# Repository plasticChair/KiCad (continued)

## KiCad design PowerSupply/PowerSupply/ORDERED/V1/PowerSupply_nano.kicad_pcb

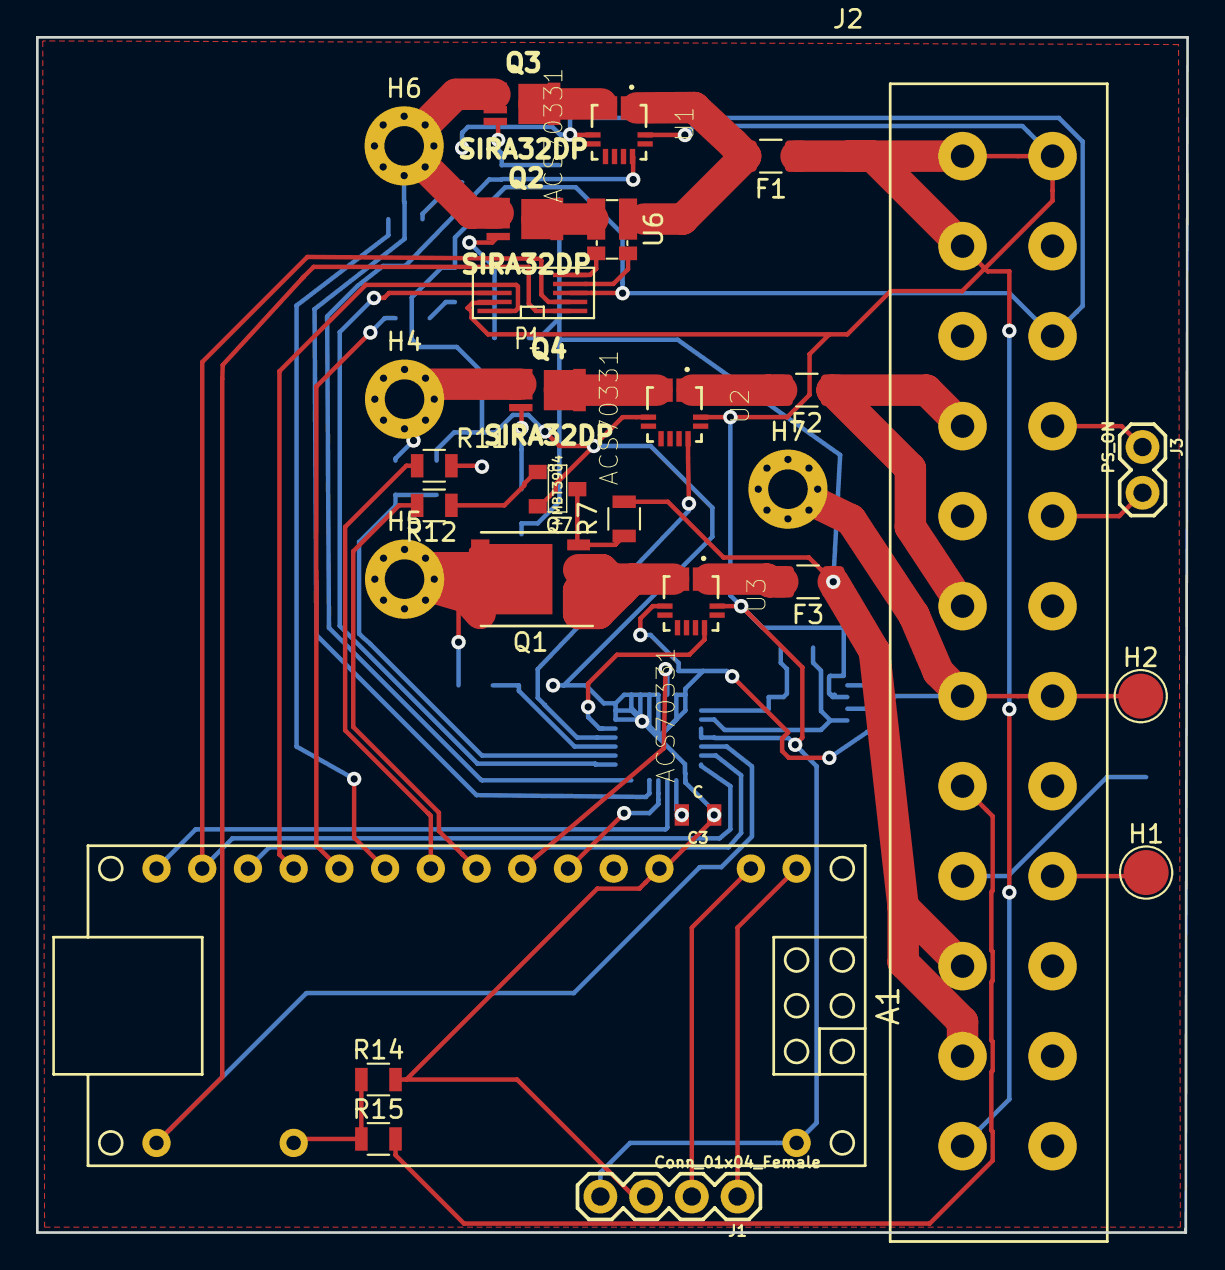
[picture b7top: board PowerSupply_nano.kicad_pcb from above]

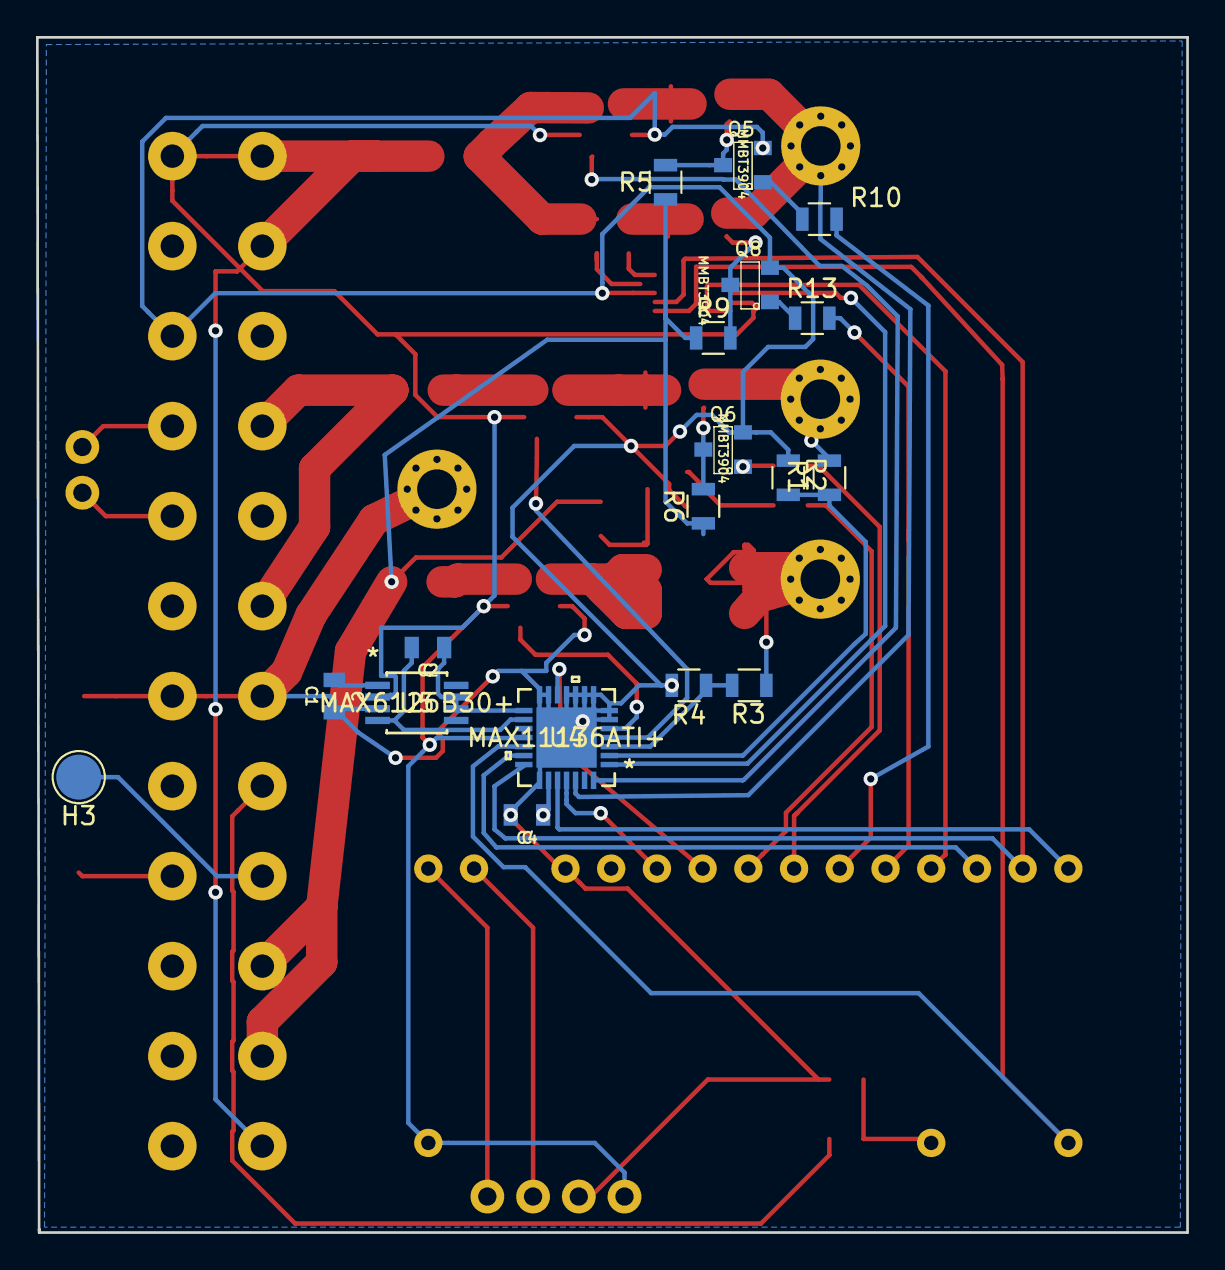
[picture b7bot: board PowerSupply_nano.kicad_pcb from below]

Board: 2 copper layers, 63.9 x 66.4 mm, 47 parts (18 on the bottom side), 53 nets.

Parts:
A1: Arduino_Nano_v3.x; arduino_nano
C1, C2, C3, C4: C; 0805
F1, F2, F3: Polyfuse; Fuse_1206_3216Metric
H1: 5V_load; TestPoint_Pad_D2.5mm
H2: 5V_load_GND; TestPoint_Pad_D2.5mm
H3: 5V_USB; TestPoint_Pad_D2.5mm
H4: 5V_OUT; MountingHole_2.2mm_M2_Pad_Via
H5: 12V_OUT; MountingHole_2.2mm_M2_Pad_Via
H6: 3p3V_OUT; MountingHole_2.2mm_M2_Pad_Via
H7: GND_OUT; MountingHole_2.2mm_M2_Pad_Via
J1: Conn_01x04_Female; 1X04
J2: ATX24; ATX_PWR_25pin
J3: PS_ON; 1X02
P1: MAX9939; uMAX-uSOP_10
Q1: SI7157DP; SO-8_PowerPAK_Vishay_Single
Q2, Q3, Q4: SIRA32DP; PowerPAK-1212-8
Q5, Q6, Q7, Q8: MMBT3904; SOT23
R1, R2, R3, R4, R5, R6, R7, R9: 10k; R_0805
R10, R11, R12, R13: 2.2k; R_0805
R14, R15: R; R_0805
U1, U2, U3: ACS70331; ALLEGRO_ACS70331EESATR-005U3
U4: MAX11136ATI+; MAX11136ATI&plus_
U5: MAX6126B30+; MAX6126B30&plus_
U6: R_0612; R_Shunt_Vishay_WSKW0612

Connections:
3V3_COURSE_EN: A1.10, R10.2
3V3_FINE_EN: A1.11, R13.2
3V3_Fine_Out: P1.8, U4.1
3V3_Out: H6.1, Q2.2, Q3.2, U4.26
5V_DIV_OUT: R1.2, R2.1, U4.2
5V_EN: A1.9, R11.2
5V_Out: H4.1, Q4.2, R1.1
5V_USB: H3.1, J2.9
12V_DIV_Out: R3.2, R4.1, U4.3
12V_EN: A1.8, R12.2
12V_Out: H5.1, Q1.5, R3.1
+3V3: A1.30, F1.1, J1.4, J2.1, J2.2, J2.12, J2.13, P1.9, U1.12, U2.12, U3.12, U4.17, U4.18, U5.2
+12V: F3.1, J2.10, J2.11, R5.1, R6.1, R7.1, R9.1
/3.3VA_D1: Q2.3, U6.4
/3.3VA_D2: Q3.3, U1.3, U1.4
/3.3V_A: F1.2, U1.1, U1.2, U6.1
/5VA: F2.1, J2.4, J2.6
/5VA_D: Q4.3, U2.3, U2.4
/5V_A: F2.2, U2.1, U2.2
/12VA_S: Q1.1, Q1.2, Q1.3, U3.3, U3.4
/12V_A: F3.2, U3.1, U3.2
CNVST_PINX: A1.7, U4.12
EOC_PINX: A1.6, U4.25
GND: A1.4, C1.1, C3.1, C4.1, H2.1, H7.1, J1.3, J2.7, J2.15, J2.19, P1.3, Q5.2, Q6.2, Q7.2, Q8.2, R2.2, R4.2, R14.2, U1.5, U2.5, U3.5, U4.6, U4.7, U4.8, U4.9, U4.10, U4.11, U4.13, U4.14, U4.22, U4.29, U5.3
unnamed: A1.1, J1.1
unnamed: A1.2, J1.2
unnamed: C1.2, U5.1
unnamed: C2.1, U4.16, U5.4
unnamed: C2.2, U4.15, U5.6, U5.7
unnamed: C3.2, C4.2, U4.23
unnamed: H1.1, J2.21
unnamed: J2.8, R15.2
unnamed: J2.16, J3.1
unnamed: J2.17, J3.2
unnamed: P1.4, U6.2
unnamed: P1.5, U6.3
unnamed: Q1.4, Q7.3, R7.2
unnamed: Q2.1, Q8.3, R9.2
unnamed: Q3.1, Q5.3, R5.2
unnamed: Q4.1, Q6.3, R6.2
unnamed: Q5.1, R10.1
unnamed: Q6.1, R11.1
unnamed: Q7.1, R12.1
unnamed: Q8.1, R13.1
unnamed: U1.10, U4.28
unnamed: U2.10, U4.4
unnamed: U3.10, U4.5
POK: A1.19, R14.1, R15.1
SPI_3V3_CS_PINX: A1.12, P1.10
SPI_ADC_CS_PINX: A1.13, U4.20
SPI_Clk_PINX: A1.16, P1.1, U4.19
SPI_MISO_PINX: A1.15, U4.24
SPI_MOSI_PINX: A1.14, P1.2, U4.21
